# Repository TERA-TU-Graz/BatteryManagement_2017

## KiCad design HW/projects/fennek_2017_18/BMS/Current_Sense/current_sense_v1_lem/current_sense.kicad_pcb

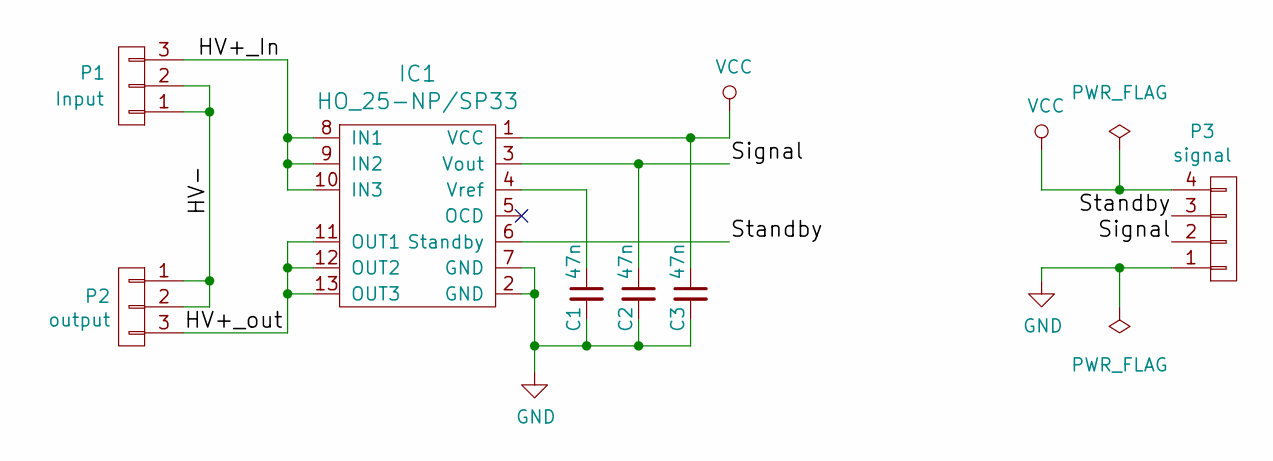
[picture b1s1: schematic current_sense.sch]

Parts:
C1, C2, C3: 47n; C_0603in
IC1: HO_25-NP/SP33; HO_25-NP_SP33
P1: Input; PhoenixContact_MSTBVA-G_03x5.08mm_Vertical
P2: output; PhoenixContact_MSTBA-G_03x5.08mm_Angled
P3: signal; Molex_PicoBlade_53261-0471_04x1.25mm_Angled

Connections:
/HV+_In: IC1.8 (IN1), IC1.9 (IN2), IC1.10 (IN3), P1.3
/HV+_out: IC1.11 (OUT1), IC1.12 (OUT2), IC1.13 (OUT3), P2.3
/HV-: P1.1, P1.2, P2.1, P2.2
/Signal: C2.1, IC1.3 (Vout), P3.2
/Standby: IC1.6 (Standby), P3.3
GND: C1.2, C2.2, C3.2, IC1.2 (GND), IC1.7 (GND), P3.1
unnamed: C1.1, IC1.4 (Vref)
VCC: C3.1, IC1.1 (VCC), P3.4

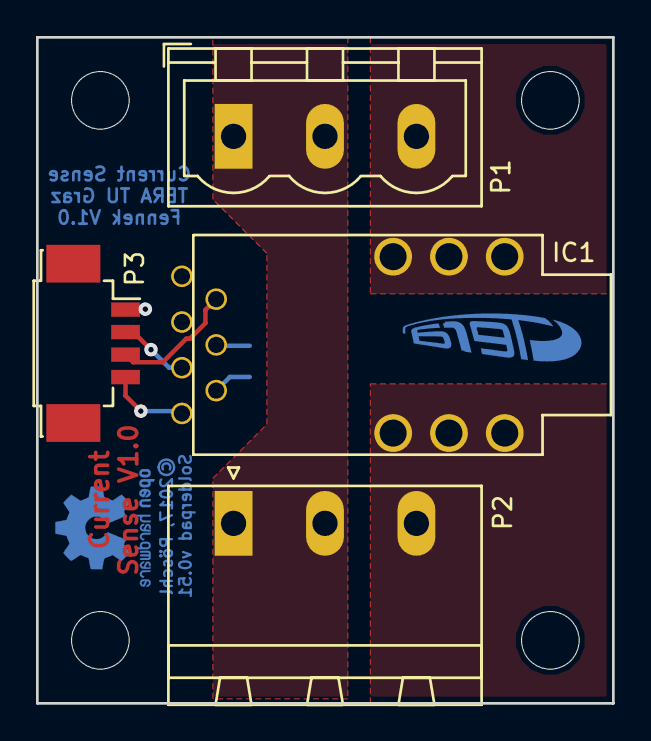
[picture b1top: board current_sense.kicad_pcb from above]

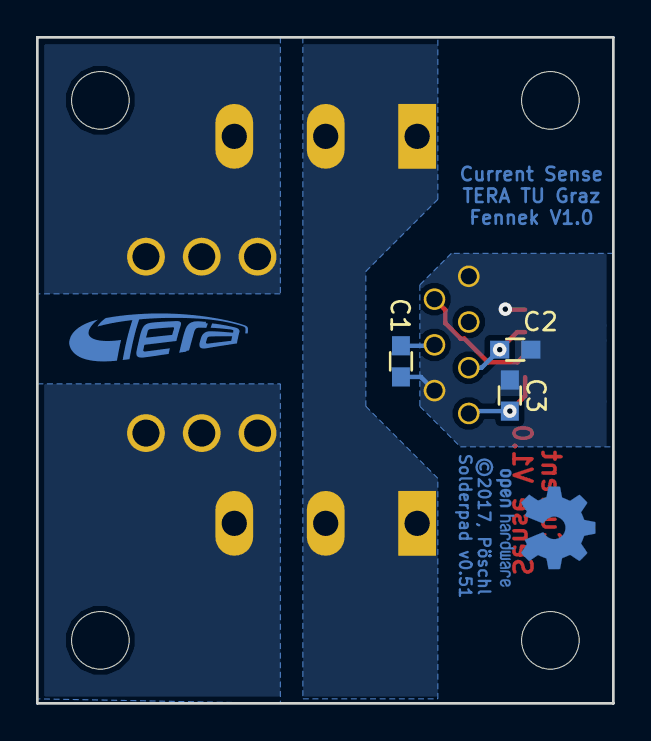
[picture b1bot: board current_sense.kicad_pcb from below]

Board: 2 copper layers, 32.0 x 37.0 mm, 8 parts (4 on the bottom side), 8 nets.

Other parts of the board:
svg2mod: G***; TERA_TextOnly_Cu_2.5x9.5mm

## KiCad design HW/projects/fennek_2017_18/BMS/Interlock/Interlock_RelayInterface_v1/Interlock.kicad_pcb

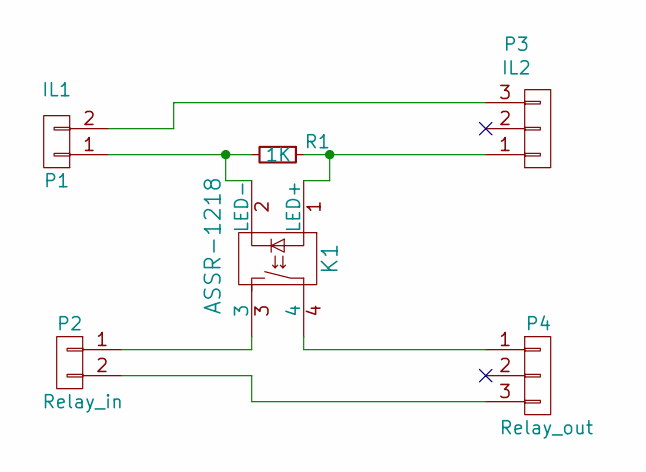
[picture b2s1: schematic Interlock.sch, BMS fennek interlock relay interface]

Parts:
K1: ASSR-1218; SO-4
P1: IL1; JST_EH_B02B-EH-A_02x2.50mm_Straight
P2: Relay_in; JST_XH_B02B-XH-A_02x2.50mm_Straight
P3: IL2; JST_EH_S03B-EH_03x2.50mm_Angled
P4: Relay_out; JST_XH_S03B-XH-A_03x2.50mm_Angled
R1: 1K; R_0603in

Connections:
unnamed: K1.1 (LED+), P3.1, R1.1
unnamed: K1.2 (LED-), P1.1, R1.2
unnamed: K1.3, P2.1
unnamed: K1.4, P4.1
unnamed: P1.2, P3.3
unnamed: P2.2, P4.3

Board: 2 copper layers, 6 parts (0 on the bottom side), 6 nets, no tracks yet.

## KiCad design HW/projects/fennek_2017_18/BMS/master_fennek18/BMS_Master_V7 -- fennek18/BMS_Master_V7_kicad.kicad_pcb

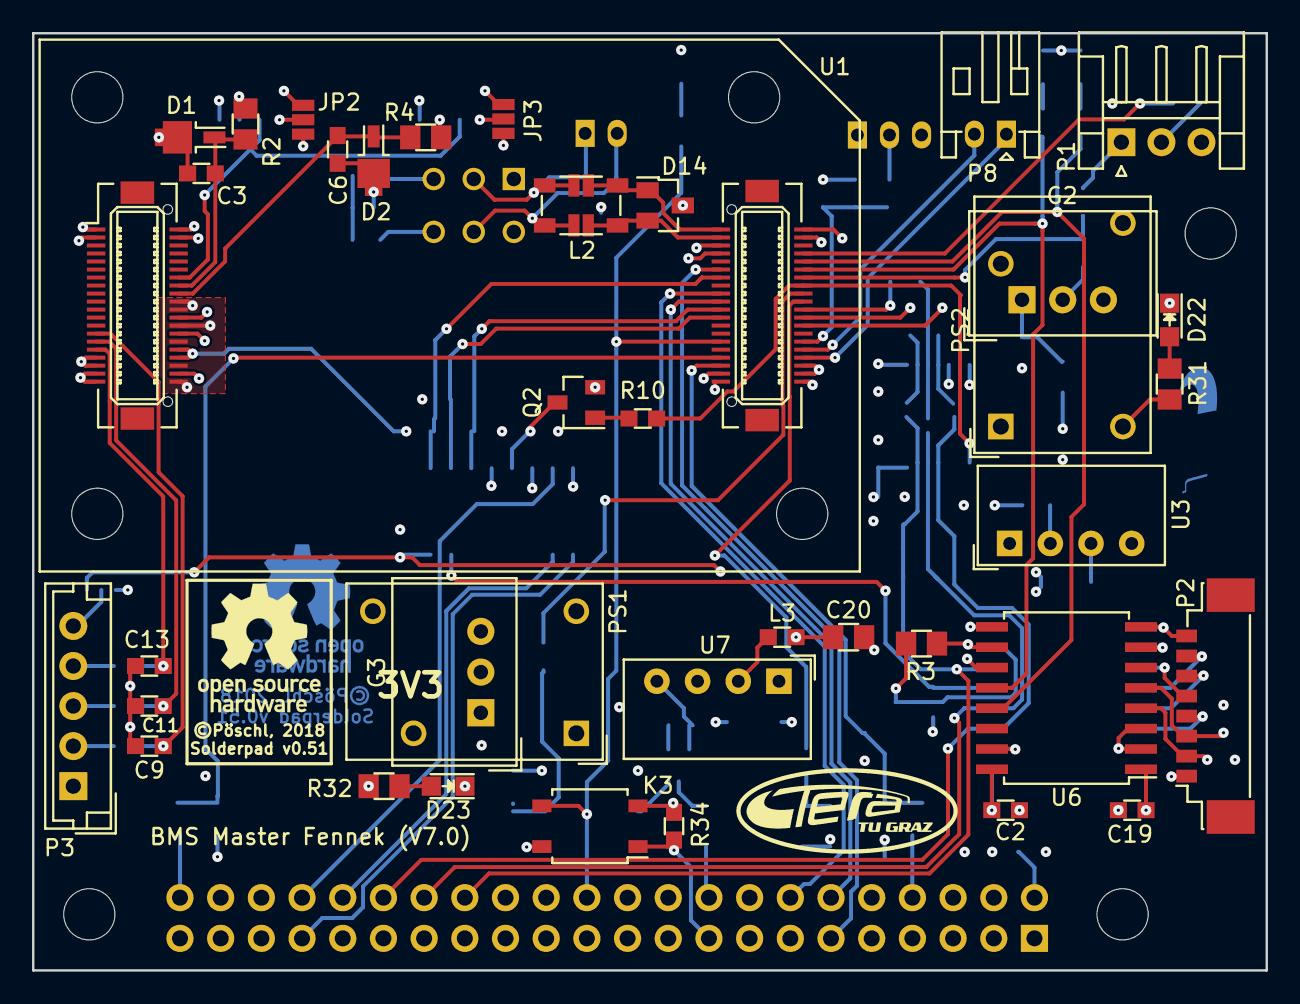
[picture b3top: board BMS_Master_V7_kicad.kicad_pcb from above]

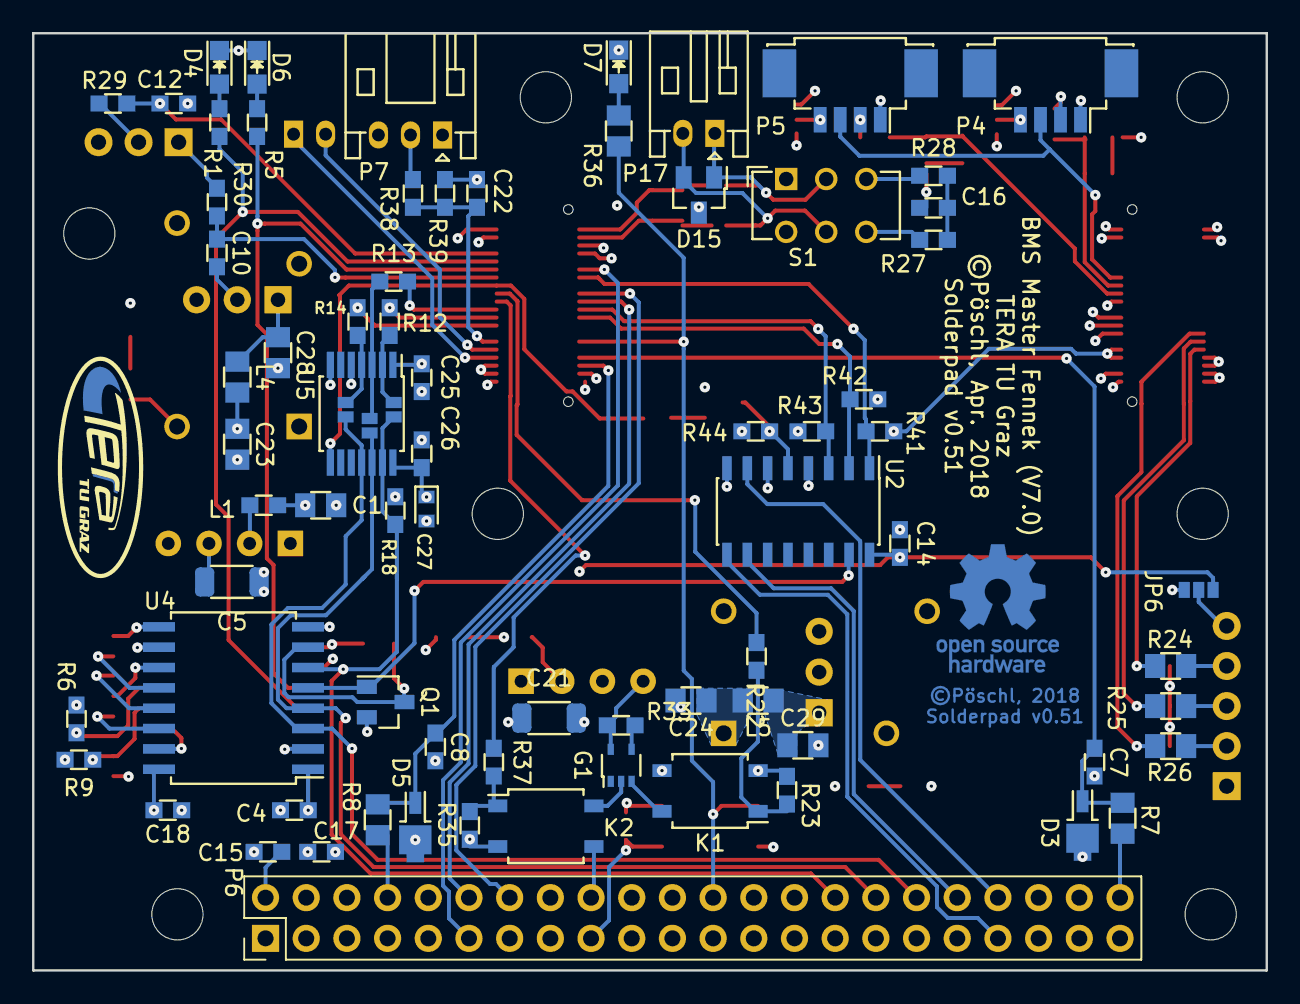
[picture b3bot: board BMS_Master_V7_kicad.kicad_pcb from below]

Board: 4 copper layers, 77.0 x 58.5 mm, 118 parts (77 on the bottom side), 92 nets.

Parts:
C1, C20: 4.7uF 25V; C_0805in
C2, C3, C4, C6, C7, C8, C9, C10, C11, C12, C13, C14, C15, C17, C18, C19, C22, C25, C26: 100n; C_0603in
C5, C21: 220pF 2kV; C_1206in_HV
C16: 47nF; C_0603in
C23, C24, C28, C29: 4u7; C_0805in
C27: 1u; TantalC_SizeM-1608mm_H0.9mm
D1, D2, D3, D5: 3V3; DO-216AA
D4: ~Alert; LED_0805
D6: ~Fault; LED_0805
D7: IL_OK; LED_0805
D14, D15: SUPPRESSOR; SOT-23
D22: 5V_OK; LED_0805
D23: 3V3_OK; LED_0805
G1: PSSI2021SAY
G2: TSR_0.5-2450; TSR_0.5
G3: TSR_0.5-2433; TSR_0.5
JP1, JP4, JP5: Jumper_NO_Small; SOLDERJUMPER_2_1mm
JP2, JP3: JUMPER3_NO; SOLDERJUMPER_3
JP6: JUMPER3_NO; SOLDERJUMPER_3_1mm
JP9, JP10: Jumper_NO_Small; SOLDERJUMPER_2
K1, K2, K3: ASSR-1218; SO-4
L1, L3: 4.7uH 50mA; L_0603in
L2: CM_CHOKE; L_ACT45B-XXX-2P_common-mode-choke
L4, L5: 3u3; L_0805in
P1: Buttons; JST_EH_S03B-EH_03x2.50mm_Angled
P2: Host_slave; Molex_PicoBlade_53398-0871_08x1.25mm_Straight
P3: ExtGPIO; JST_EH_B05B-EH-A_05x2.50mm_Straight
P4, P5: LEM; Molex_PicoBlade_53261-0471_04x1.25mm_Angled
P6: CONN_02X22; DW-22-08-L-D-200
P7: WheelSpeed; JST_PH_S3B-PH-K_03x2.00mm_Angled
P8, P17: CAN_CON_2pol; JST_PH_S2B-PH-K_02x2.00mm_Angled
PS1: Stepdown_v6-3V3; DCDC_Stepdown_v6
PS2: Stepdown_v6-5V; DCDC_Stepdown_v6
Q1, Q2: BSS205N
R1, R5: 5k1; R_0603in
R2, R4, R7, R8, R24, R25, R26: 1K; R_0805in
R3: 10k; R_0805in
R6, R9, R18: 100k; R_0603in
R10: 1k; R_0603in
R12, R13, R14: 100R; R_0603in
R22, R37: 470; R_0603in
R23, R29, R30, R34, R35: 1K; R_0603in
R27, R28: 60R; R_0603in
R31, R36: 5k1; R_0805in
R32: 2k2; R_0805in
R33: 120R; R_0603in
R38: 0R; R_0603in
R39: 22k; R_0603in
R41, R42, R43, R44: 10k; R_0603in
S1: SWITCH_DPDT; CuK_JS202011CQN_DPDT
U1: STM32f4_board_v3-1; STM32f4-board_v3-1
U2: SN74HC138DR
U3: Muarta_LME1205SC; Muarta_LME-SIP
U4, U6: ISO7241
U5: MAX3390EEUD
U7: Muarta_LME1212SC; Muarta_LME-SIP
svg2mod: G***; TERA_Logo_SilkS_5x12.5mm
svg2mod#2: G***; TERA_Logo_SilkS_and_Cu_5x12.5mm

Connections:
+3V3: C25.2, G3.3, JP2.3, JP3.3, JP6.1, P6.6, P6.42, PS1.2, R32.1, U1.2, U1.17, U1.18, U1.22, U1.27, U1.29, U1.39, U1.44, U1.59, U1.62, U1.63, U1.79, U5.1
+5V: C2.1, C4.1, C14.2, C26.1, C27.1, G2.3, JP2.1, JP3.1, JP6.3, K3.4, P1.3, P6.28, P7.3, PS2.2, R3.1, R31.1, R41.1, R42.1, R43.1, R44.2, U1.24, U1.25, U2.6, U2.16, U4.1, U5.14, U6.10, U6.16
+5V_SLAVE: C18.2, C19.2, P2.1, U3.4, U4.10, U4.16, U6.1, U6.7
+12V: C1.1, C17.2, C20.1, C23.1, C24.1, L1.2, L3.2, L4.2, L5.2, P6.4, PS1.1, PS2.1
/12V_Relay_Fault: P6.11, U1.46
/Alegro_1: P6.44, R7.1
/Alegro_1_Filtered: C7.1, D3.1, R7.2, U1.57
/Alegro_2: P6.8, R8.1
/Alegro_2_Filtered: C8.1, D5.1, R8.2, U1.58
/Button_Off: C10.1, R30.2, U1.74
/Button_On: C12.1, R29.2, U1.77
/CAN/CAN1+: P8.2, U1.65
/CAN/CAN1-: P8.1, U1.64
/CAN/CAN2+: D14.2, JP10.1, L2.2, U1.42
/CAN/CAN2-: D14.1, JP9.1, L2.3, U1.41
/CAN/CANperi+: D15.2, JP10.2, L2.1, P17.2, S1.5
/CAN/CANperi-: D15.1, JP9.2, L2.4, P17.1, S1.2
/CS_B0: R41.2, U1.47, U2.1
/CS_B1: R42.2, U1.52, U2.2
/CS_B2: R43.2, U1.51, U2.3
/EXT_GPIO_1: C13.1, R24.2, U1.16
/EXT_GPIO_2: C11.1, R25.2, U1.15
/EXT_GPIO_3: C9.1, R26.2, U1.14
/IL_next+: K2.3, P6.18
/IL_next-: K3.1, P6.17, R34.1
/Interlock/IL_Iconst: G1.2, K2.4
/Interlock_OK: K3.3, P6.24, R36.2, U1.55
/Interlock_On1: R22.2, U1.72
/Interlock_On2: R37.1, U1.71
/LEM1: C3.1, D1.1, R2.2, U1.33
/LEM2: C6.1, D2.1, R4.2, U1.32
/LEM_Standby: P4.3, P5.3, U1.34
/MISO: R12.2, U1.69
/MOSI: R13.2, U1.70
/Main Connector/+12VDC_BMS_Switched: C15.2, P6.2
/Main_Fault: P6.12, U1.50
/NALERT: R1.1, U1.76, U6.13
/NCS_12V_Relay: P6.37, U2.9
/NCS_MainRelay: P6.36, U2.10
/NCS_PreCharge: P6.38, U2.7
/NFAULT: R5.1, U1.75, U6.12
/Precharge_Fault: P6.14, U1.49
/SCLK: R14.2, U1.68
/SPI_CLK_5V: JP5.2, P6.34, U4.3, U5.11
/SPI_CS: R10.2, U1.73, U5.8
/SPI_Controller/MISO_1: JP1.1, R12.1, U5.2
/SPI_Controller/MOSI_1: JP4.1, R13.1, U5.3
/SPI_Controller/NCS1: Q1.1, U2.15, U4.5
/SPI_Controller/SCLK_1: JP5.1, R14.1, U5.4
/SPI_Controller/SPI Isolator/MISO_slave: P2.5, U4.11
/SPI_Controller/SPI Isolator/MOSI_Slave: P2.6, U4.13
/SPI_Controller/SPI Isolator/NCS_Slave: P2.7, U4.12
/SPI_Controller/SPI Isolator/SCLK_slave: P2.4, U4.14
/SPI_Controller/SPI Isolator/~Alert_slave: P2.2, R9.1, U6.4
/SPI_Controller/SPI Isolator/~Fault_slave: P2.3, R6.1, U6.5
/SPI_Controller/SPI_NCS_5V: Q2.3, R44.1, U2.5
/SPI_MISO_5V: JP1.2, P6.30, R18.1, U4.6, U5.13
/SPI_MOSI_5V: JP4.2, P6.32, U4.4, U5.12
/WheelSpeed: C22.1, R38.2, R39.2, U1.66
GND: C1.2, C2.2, C3.2, C4.2, C5.1, C6.2, C7.2, C8.2, C9.2, C10.2, C11.2, C12.2, C13.2, C14.1, C15.1, C16.2, C17.1, C20.2, C21.1, C22.2, C23.2, C24.2, C25.1, C26.2, C27.2, C28.2, C29.2, D1.2, D2.2, D3.2, D4.1, D5.2, D6.1, D7.1, D14.3, D15.3, D22.1, D23.1, G2.2, G3.2, K1.2, K2.2, P3.1, P4.1, P5.1, P6.1, P6.3, P6.5, P6.7, P6.9, P6.10, P6.13, P6.21, P6.22, P6.23, P6.25, P6.26, P6.27, P6.29, P6.31, P6.33, P6.35, P6.39, P6.40, P6.41, P6.43, P7.1, PS1.3, PS1.4, PS2.3, PS2.4, Q1.2, Q2.2, R18.2, R23.2, R35.2, R39.1, U1.1, U1.19, U1.20, U1.21, U1.23, U1.26, U1.28, U1.30, U1.31, U1.40, U1.43, U1.60, U1.61, U1.80, U2.4, U2.8, U3.1, U4.2, U4.8, U5.5, U5.7, U6.9, U6.11, U6.15, U7.1
GND_slave: C5.2, C18.1, C19.1, P2.8, R6.2, R9.2, U3.3, U4.9, U4.15, U6.2, U6.3, U6.8
IL_V+: G1.5, R33.1, U7.4
IL_V-: C21.2, K1.3, K3.2, R34.2, U7.3
unnamed: C16.1, R27.2, R28.2
unnamed: C28.1, G2.1, L4.1
unnamed: C29.1, G3.1, L5.1
unnamed: D4.2, R1.2
unnamed: D6.2, R5.2
unnamed: D7.2, R36.1
unnamed: D22.2, R31.2
unnamed: D23.2, R32.2
unnamed: G1.3, K1.4
unnamed: G1.4, R33.2
unnamed: JP2.2, P4.4
unnamed: JP3.2, P5.4
unnamed: JP6.2, P3.5
unnamed: K1.1, R22.1, R23.1
unnamed: K2.1, R35.1, R37.2
unnamed: L1.1, U3.2
unnamed: L3.1, U7.2
unnamed: P1.1, R30.1
unnamed: P1.2, R29.1
unnamed: P3.2, R26.1
unnamed: P3.3, R25.1
unnamed: P3.4, R24.1
unnamed: P4.2, R2.1
unnamed: P5.2, R4.1
unnamed: P7.2, R38.1
unnamed: Q1.3, R3.2, U4.7
unnamed: Q2.1, R10.1
unnamed: R27.1, S1.6
unnamed: R28.1, S1.3

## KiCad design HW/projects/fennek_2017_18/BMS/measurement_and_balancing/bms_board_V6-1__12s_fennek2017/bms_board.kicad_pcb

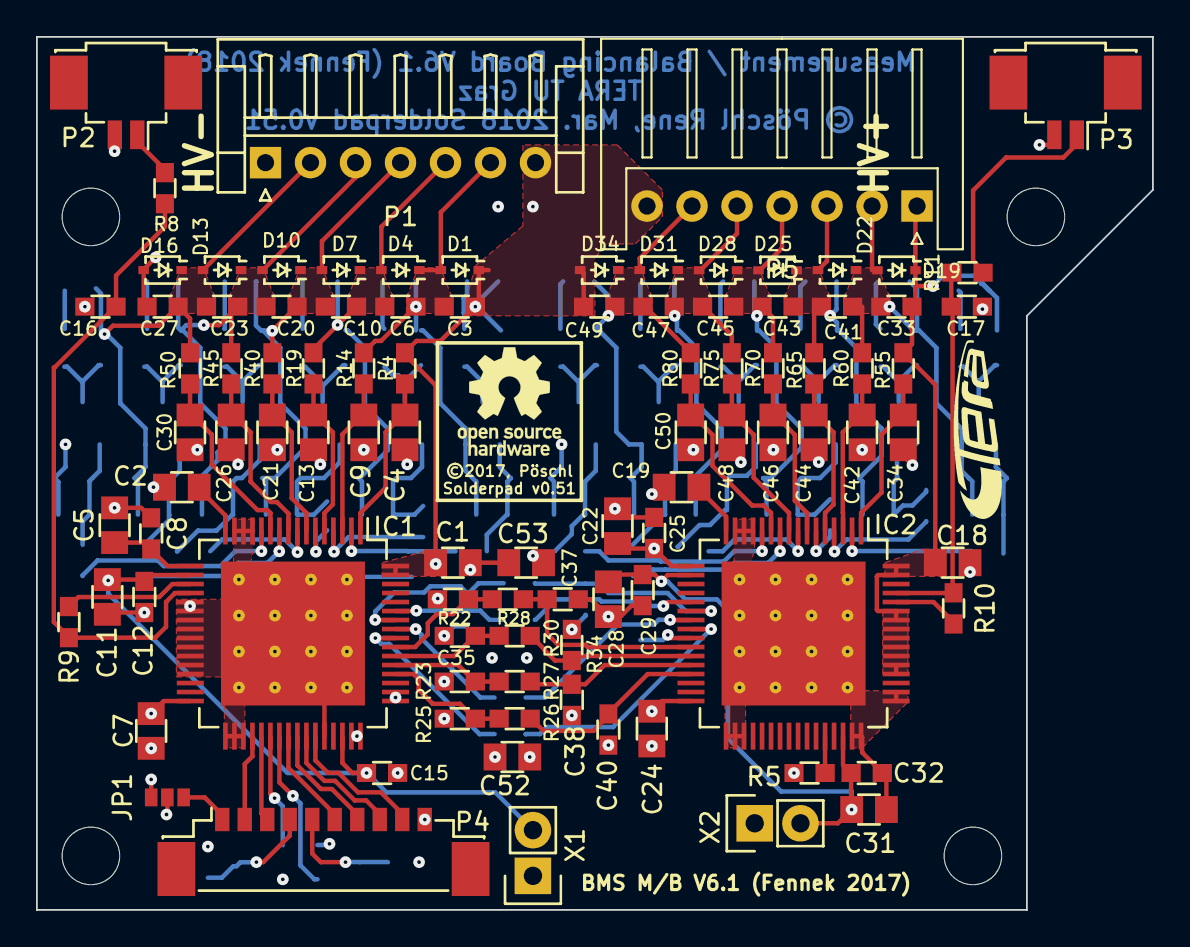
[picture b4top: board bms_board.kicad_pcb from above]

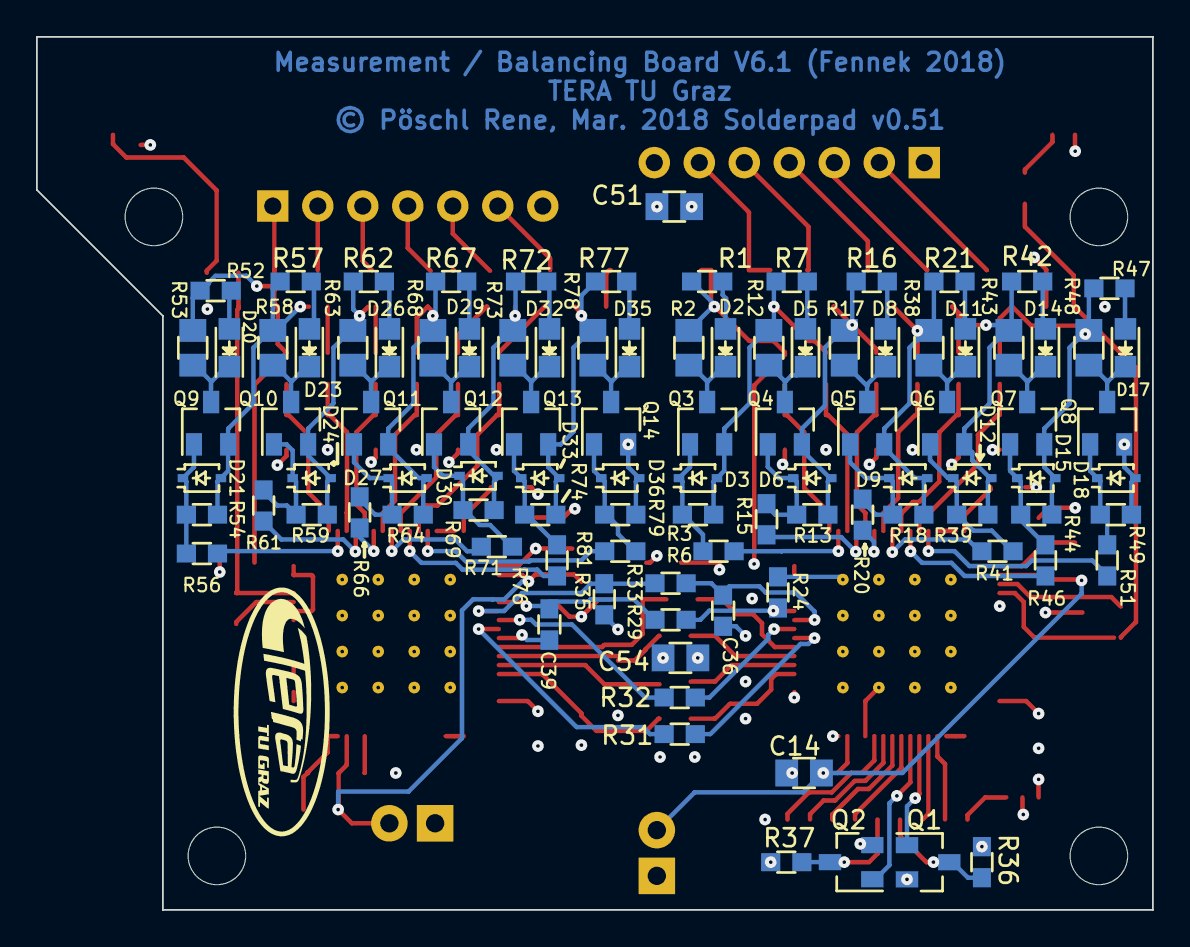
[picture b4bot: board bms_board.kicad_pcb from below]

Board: 4 copper layers, 62.0 x 48.5 mm, 197 parts (100 on the bottom side), 116 nets.

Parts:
C1, C4, C9, C13, C18, C21, C26, C30, C34, C42, C44, C46, C48, C50, C51, C52, C53, C54: 100n 50V; C_0805in
C2, C19: 10u; C_0805in
C3, C6, C8, C10, C12, C15, C20, C23, C25, C27, C29, C32, C33, C41, C43, C45, C47, C49: 100n; C_0603in
C5, C7, C11, C14, C22, C24, C28, C31: 2.2u; C_0805in
C16, C17: 47n; C_0603in
C35, C36, C37, C38, C39, C40: 33p; C_0603in
D1, D3, D4, D6, D7, D9, D10, D12, D13, D15, D16, D18, D19, D21, D22, D24, D25, D27, D28, D30, D31, D33, D34, D36: 5.1V; SOD-323
D2, D5, D8, D11, D14, D17, D20, D23, D26, D29, D32, D35: LED; LED_0805
IC1, IC2: TI-bq76pl536; TI_bq76PL536
JP1: JUMPER3_NO; SOLDERJUMPER_3_1mm
P1: CONN_01X07; JST_EH_S07B-EH_07x2.50mm_Angled
P2: TS1; Molex_PicoBlade_53261-0271_02x1.25mm_Angled
P3: TS2; Molex_PicoBlade_53261-0271_02x1.25mm_Angled
P4: Host_Interface; Molex_PicoBlade_53398-1071_10x1.25mm_Straight
P5: CONN_01X07; JST_XH_S07B-XH-A_07x2.50mm_Angled
Q1, Q2, Q3, Q4, Q5, Q6, Q7, Q8, Q9, Q10, Q11, Q12, Q13, Q14: BSS205N
R1, R7, R16, R21, R42, R47, R52, R57, R62, R67, R72, R77: 2K2; R_0603in
R2, R12, R17, R38, R43, R48, R53, R58, R63, R68, R73, R78: 180R; R_0805in
R3, R13, R18, R22, R23, R24, R25, R39, R44, R49, R54, R59, R64, R69, R74, R79: 2M; R_0603in
R4, R6, R14, R15, R19, R20, R26, R27, R28, R29, R30, R31, R32, R33, R40, R41, R45, R46, R50, R51, R55, R56, R60, R61, R65, R66, R70, R71, R75, R76, R80, R81: 1K; R_0603in
R5: 100K; R_0603in
R8, R11: 1.47K; R_0603in
R9, R10: 1.82K; R_0603in
R34, R35: 510K; R_0603in
R36, R37: 10K; R_0603in
X1, X2: Prog_Voltage; Socket_Strip_Straight_1x02
svg2mod: G***; TERA_Logo_SilkS_5x12.5mm
svg2mod#2: G***; TERA_TextOnly_SilkS_2.5x9.5mm

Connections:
+5V: C7.1, C16.1, IC1.32, JP1.1, P2.2
+BATT: C18.2, C33.1, D19.1, IC2.52, IC2.53, IC2.54, IC2.55, IC2.56, IC2.57, IC2.58, IC2.59, IC2.63, IC2.64, P5.1, R52.1, R53.1, R55.2
/5V_C2: C17.1, C24.1, IC2.32, P3.2, R34.1, R35.1
/Chip1/+5V_LDOA: C5.1, C8.1, IC1.17
/Chip1/Alert_H: IC1.38, Q1.1
/Chip1/BalanceCell1/VCn: C30.1, IC1.11, R50.1
/Chip1/BalanceCell2/VCn: C26.1, IC1.9, R45.1
/Chip1/BalanceCell3/VCn: C21.1, IC1.7, R40.1
/Chip1/BalanceCell4/VCn: C13.1, IC1.5, R19.1
/Chip1/BalanceCell5/VCn: C9.1, IC1.3, R14.1
/Chip1/BalanceCell6/VCn: C4.1, IC1.1, R4.1
/Chip1/CB1: IC1.12, R51.1
/Chip1/CB2: IC1.10, R46.1
/Chip1/CB3: IC1.8, R41.1
/Chip1/CB4: IC1.6, R20.1
/Chip1/CB5: IC1.4, R15.1
/Chip1/CB6: IC1.2, R6.1
/Chip1/CONV_H: IC1.36, P4.2
/Chip1/CS_H: IC1.43, P4.9
/Chip1/DRDY_H: IC1.37, P4.3
/Chip1/Fault_H: IC1.39, Q2.1
/Chip1/LDODx: C11.1, C12.1, C14.1, C15.1, IC1.18, IC1.46, X1.2
/Chip1/SCLK_H: IC1.40, P4.6
/Chip1/SDI_H: IC1.42, P4.8
/Chip1/SDO_H: IC1.41, P4.7
/Chip1/TS1+: C16.2, IC1.20, R8.1, R9.1
/Chip1/TS1-: IC1.19, R9.2
/Chip1/VC1: C23.2, C27.1, D13.2, D15.2, D16.1, P1.2, Q7.2, R44.2, R47.1, R48.1, R50.2
/Chip1/VC2: C20.2, C23.1, D10.2, D12.2, D13.1, P1.3, Q6.2, R39.2, R42.1, R43.1, R45.2
/Chip1/VC3: C10.2, C20.1, D7.2, D9.2, D10.1, P1.4, Q5.2, R18.2, R21.1, R38.1, R40.2
/Chip1/VC4: C6.2, C10.1, D4.2, D6.2, D7.1, P1.5, Q4.2, R13.2, R16.1, R17.1, R19.2
/Chip1/VC5: C3.2, C6.1, D1.2, D3.2, D4.1, P1.6, Q3.2, R3.2, R7.1, R12.1, R14.2
/Chip2/+5V_LDOA: C22.1, C25.1, IC2.17, R5.1
/Chip2/BalanceCell1/VCn: C50.1, IC2.11, R80.1
/Chip2/BalanceCell2/VCn: C48.1, IC2.9, R75.1
/Chip2/BalanceCell3/VCn: C46.1, IC2.7, R70.1
/Chip2/BalanceCell4/VCn: C44.1, IC2.5, R65.1
/Chip2/BalanceCell5/VCn: C42.1, IC2.3, R60.1
/Chip2/BalanceCell6/VCn: C34.1, IC2.1, R55.1
/Chip2/CB1: IC2.12, R81.1
/Chip2/CB2: IC2.10, R76.1
/Chip2/CB3: IC2.8, R71.1
/Chip2/CB4: IC2.6, R66.1
/Chip2/CB5: IC2.4, R61.1
/Chip2/CB6: IC2.2, R56.1
/Chip2/HSEL: IC2.44, R5.2
/Chip2/LDODx: C28.1, C29.1, C31.1, C32.1, IC2.18, IC2.46, X2.2
/Chip2/TS2+: C17.2, IC2.61, R10.1, R11.1
/Chip2/TS2-: IC2.60, R10.2
/Chip2/VC1: C47.2, C49.1, D31.2, D33.2, D34.1, P5.6, Q13.2, R74.2, R77.1, R78.1, R80.2
/Chip2/VC2: C45.2, C47.1, D28.2, D30.2, D31.1, P5.5, Q12.2, R69.2, R72.1, R73.1, R75.2
/Chip2/VC3: C43.2, C45.1, D25.2, D27.2, D28.1, P5.4, Q11.2, R64.2, R67.1, R68.1, R70.2
/Chip2/VC4: C41.2, C43.1, D22.2, D24.2, D25.1, P5.3, Q10.2, R59.2, R62.1, R63.1, R65.2
/Chip2/VC5: C33.2, C41.1, D19.2, D21.2, D22.1, P5.2, Q9.2, R54.2, R57.1, R58.1, R60.2
/Daisychain/Alert_1: IC1.57, R32.1
/Daisychain/Alert_2: IC2.23, R32.2
/Daisychain/CONV_1: IC1.59, R24.2, R29.1
/Daisychain/CONV_2: C39.1, IC2.21, R29.2
/Daisychain/CS_1: IC1.52, R25.2, R26.1
/Daisychain/CS_2: C40.1, IC2.29, R26.2
/Daisychain/DRDY_1: C36.2, IC1.58, R33.1
/Daisychain/DRDY_2: IC2.22, R33.2, R35.2
/Daisychain/Fault_1: IC1.56, R31.1
/Daisychain/Fault_2: IC2.24, R31.2
/Daisychain/SCLK_1: IC1.55, R22.2, R28.1
/Daisychain/SCLK_2: C37.1, IC2.26, R28.2
/Daisychain/SDI_1: IC1.53, R23.2, R27.1
/Daisychain/SDI_2: C38.1, IC2.28, R27.2
/Daisychain/SDO_1: C35.2, IC1.54, R30.1
/Daisychain/SDO_2: IC2.27, R30.2, R34.2
/Host_connect/+5V_DO: JP1.2, R36.1, R37.1
/Host_connect/+5V_Host: JP1.3, P4.1
/Host_connect/NALERT_H: P4.4, Q1.3, R36.2
/Host_connect/NFAULT_H: P4.5, Q2.3, R37.2
GND: C1.1, C2.2, C4.2, C5.2, C7.2, C8.2, C9.2, C11.2, C12.2, C13.2, C14.2, C15.2, C21.2, C26.2, C27.2, C30.2, C51.2, C52.2, C53.2, C54.2, D16.2, D18.2, IC1.13, IC1.14, IC1.15, IC1.21, IC1.22, IC1.23, IC1.24, IC1.25, IC1.26, IC1.27, IC1.28, IC1.29, IC1.33, IC1.34, IC1.35, IC1.44, IC1.47, IC1.48, IC1.49, IC1.50, IC1.65, P1.1, P4.10, Q1.2, Q2.2, Q8.2, R22.1, R23.1, R24.1, R25.1, R49.2, X1.1
unnamed: C2.1, IC1.16
unnamed: C19.1, IC2.16
unnamed: D2.1, Q3.3, R2.2
unnamed: D2.2, R1.2
unnamed: D3.1, Q3.1, R3.1, R6.2
unnamed: D5.1, Q4.3, R12.2
unnamed: D5.2, R7.2
unnamed: D6.1, Q4.1, R13.1, R15.2
unnamed: D8.1, Q5.3, R17.2
unnamed: D8.2, R16.2
unnamed: D9.1, Q5.1, R18.1, R20.2
unnamed: D11.1, Q6.3, R38.2
unnamed: D11.2, R21.2
unnamed: D12.1, Q6.1, R39.1, R41.2
unnamed: D14.1, Q7.3, R43.2
unnamed: D14.2, R42.2
unnamed: D15.1, Q7.1, R44.1, R46.2
unnamed: D17.1, Q8.3, R48.2
unnamed: D17.2, R47.2
unnamed: D18.1, Q8.1, R49.1, R51.2
unnamed: D20.1, Q9.3, R53.2
unnamed: D20.2, R52.2
unnamed: D21.1, Q9.1, R54.1, R56.2
unnamed: D23.1, Q10.3, R58.2
unnamed: D23.2, R57.2
unnamed: D24.1, Q10.1, R59.1, R61.2
unnamed: D26.1, Q11.3, R63.2
unnamed: D26.2, R62.2
unnamed: D27.1, Q11.1, R64.1, R66.2
unnamed: D29.1, Q12.3, R68.2
unnamed: D29.2, R67.2
unnamed: D30.1, Q12.1, R69.1, R71.2
unnamed: D32.1, Q13.3, R73.2
unnamed: D32.2, R72.2
unnamed: D33.1, Q13.1, R74.1, R76.2
unnamed: D35.1, Q14.3, R78.2
unnamed: D35.2, R77.2
unnamed: D36.1, Q14.1, R79.1, R81.2
unnamed: P2.1, R8.2
unnamed: P3.1, R11.2
Vmiddle: C1.2, C3.1, C18.1, C19.2, C22.2, C24.2, C25.2, C28.2, C29.2, C31.2, C32.2, C34.2, C35.1, C36.1, C37.2, C38.2, C39.2, C40.2, C42.2, C44.2, C46.2, C48.2, C49.2, C50.2, C51.1, C52.1, C53.1, C54.1, D1.1, D34.2, D36.2, IC1.63, IC1.64, IC2.13, IC2.14, IC2.15, IC2.25, IC2.33, IC2.34, IC2.35, IC2.47, IC2.48, IC2.49, IC2.50, IC2.65, P1.7, P5.7, Q14.2, R1.1, R2.1, R4.2, R79.2, X2.1

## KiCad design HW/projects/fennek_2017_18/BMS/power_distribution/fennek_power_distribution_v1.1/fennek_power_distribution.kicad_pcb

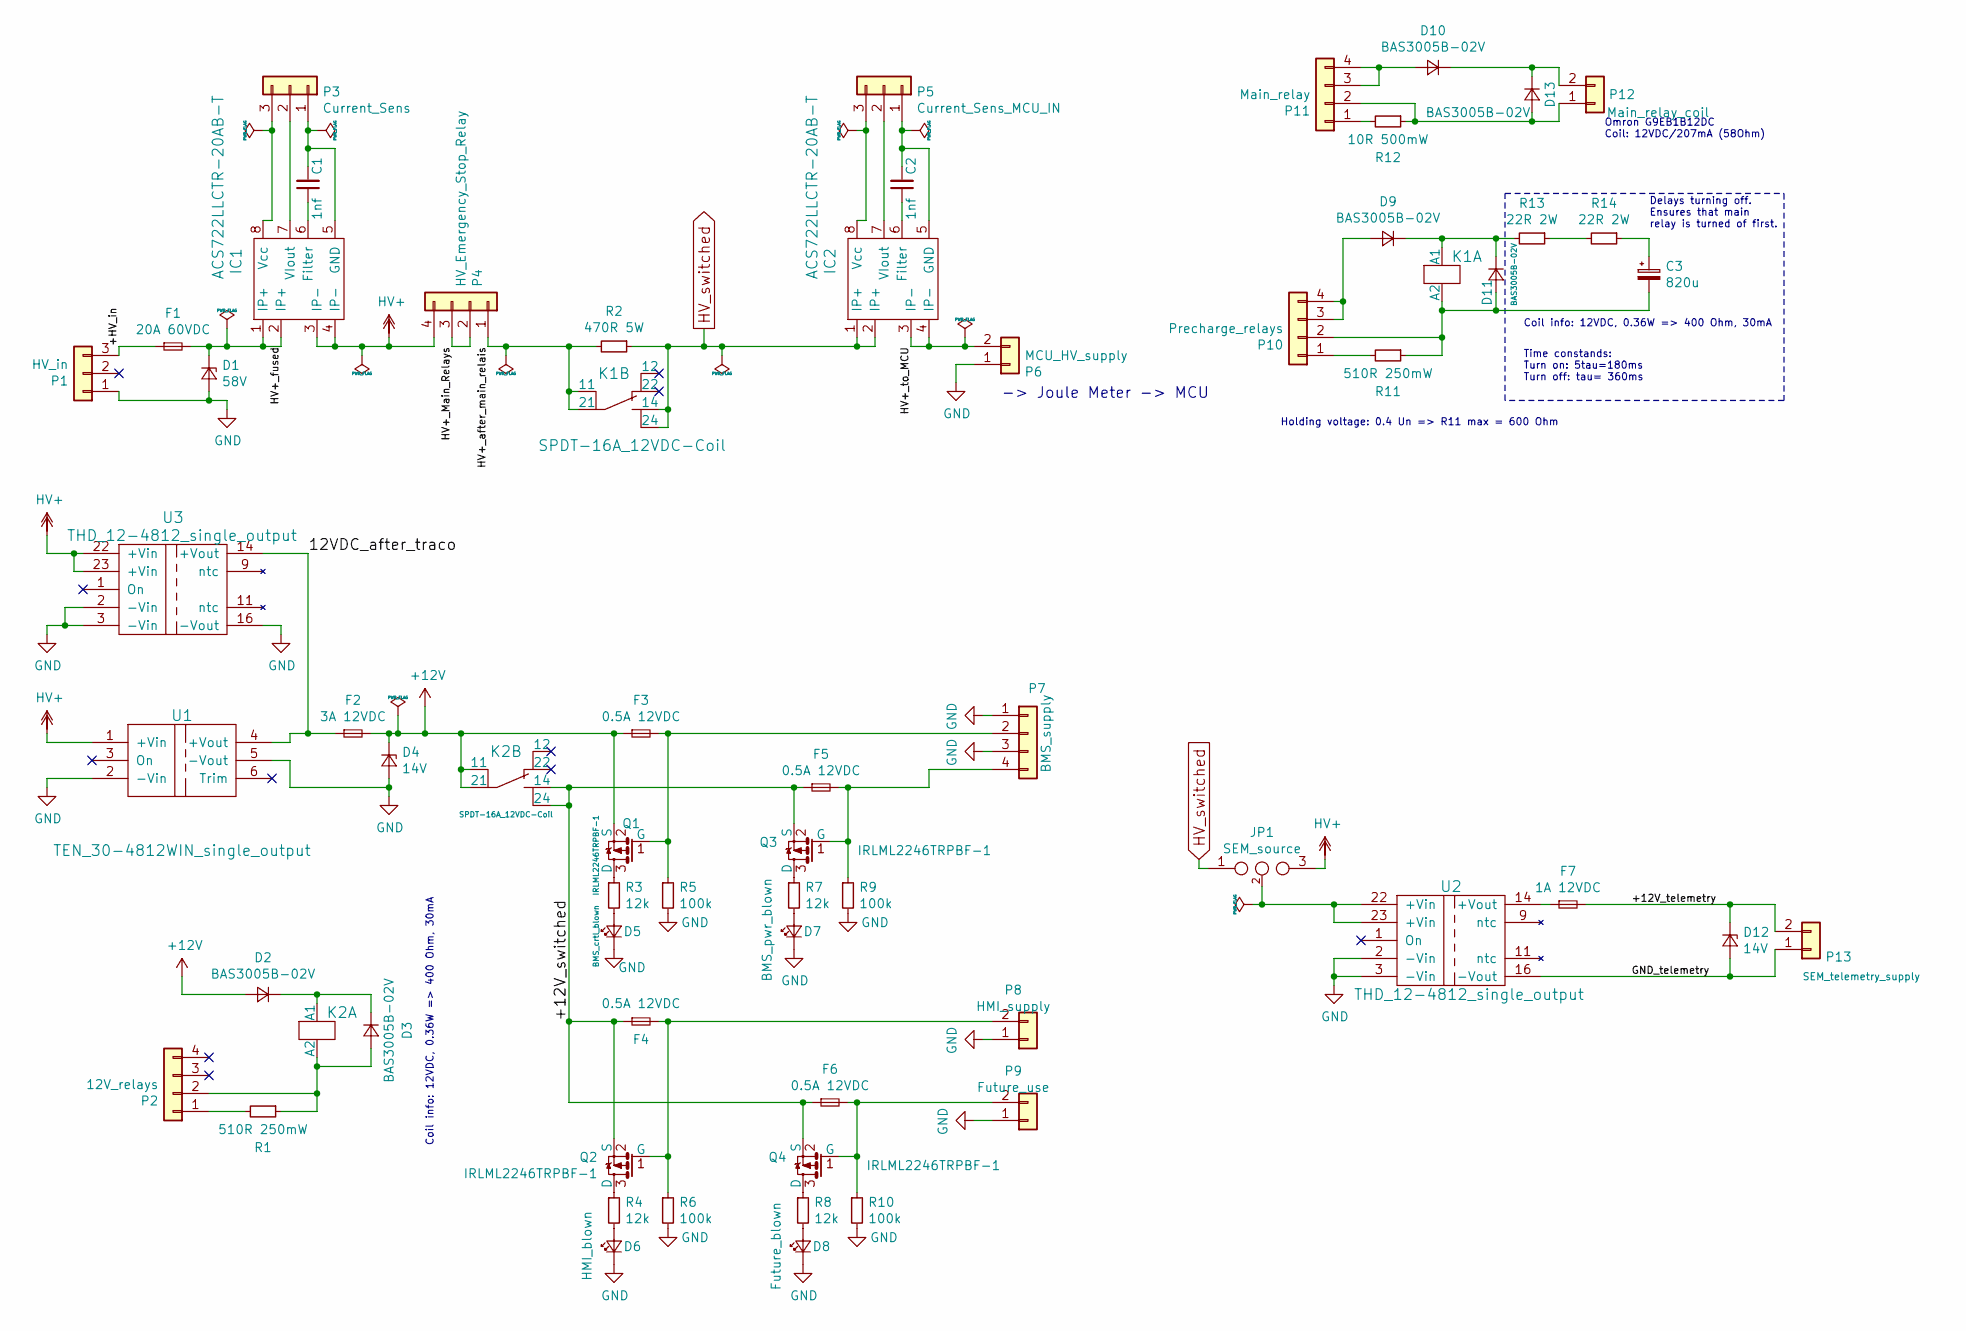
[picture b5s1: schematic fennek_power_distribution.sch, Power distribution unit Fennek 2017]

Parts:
C1, C2: 1nf; C_0603in
C3: 820u; c_elec_10x10mm
D1: 58V; DO-214AA_with_vias_in_pad
D2, D3, D9, D10, D11, D13: BAS3005B-02V; BAS3005B-02V__sc79
D4, D12: 14V; SOD128_with_vias_in_pad
D5: BMS_crtl_blown; LED_0805
D6: HMI_blown; LED_0805
D7: BMS_pwr_blown; LED_0805
D8: Future_blown; LED_0805
F1: 20A 60VDC; Fuse_holder_6.3x32mm_Schruter_0031.2520
F2: 3A 12VDC; Fuse_Phoenix_SI-H-FKS_15
F3, F4, F5, F6: 0.5A 12VDC; Fuse_0603in
F7: 1A 12VDC; Fuse_Phoenix_SI-H-FKS_15
IC1, IC2: ACS722LLCTR-20AB-T; ACS7xx
JP1: SEM_source; SOLDERJUMPER_3
K1, K2: SPDT-16A_12VDC-Coil; Finder-41.61.9.012.0010_SPDT-16A_12VDC-Coil
P1: HV_in; PhoenixContact_MSTBA-G_03x5.08mm_Angled
P2: 12V_relays; JST_EH_B04B-EH-A_04x2.50mm_Straight
P3: Current_Sens; Molex_PicoBlade_53398-0371_03x1.25mm_Straight
P4: HV_Emergency_Stop_Relay; PhoenixContact_MSTBA-G_04x5.08mm_Angled
P5: Current_Sens_MCU_IN; Molex_PicoBlade_53398-0371_03x1.25mm_Straight
P6: MCU_HV_supply; PhoenixContact_MSTB-GF_02x5.08mm_Angled_ThreadedFlange
P7: BMS_supply; JST_XH_B04B-XH-A_04x2.50mm_Straight
P8: HMI_supply; JST_XH_B02B-XH-A_02x2.50mm_Straight
P9: Future_use; JST_XH_B02B-XH-A_02x2.50mm_Straight
P10: Precharge_relays; JST_EH_B04B-EH-A_04x2.50mm_Straight
P11: Main_relay; JST_EH_B04B-EH-A_04x2.50mm_Straight
P12: Main_relay_coil; JST_EH_B02B-EH-A_02x2.50mm_Straight
P13: SEM_telemetry_supply; PhoenixContact_MC-GF_02x3.50mm_Angled_ThreadedFlange
Q1, Q2, Q3, Q4: IRLML2246TRPBF-1
R1, R11: 510R 250mW; R_1206in
R2: 470R 5W; TE_SMW-5W
R3, R4, R7, R8: 12k; R_0603in
R5, R6, R9, R10: 100k; R_0603in
R12: 10R 500mW; R_1210in
R13, R14: 22R 2W; R_2512in
U1: TEN_30-4812WIN_single_output; TEN_30-xxxx
U2, U3: THD_12-4812_single_output; THD_12-xxxx

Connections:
+12V: D2.2 (A), D4.1 (K), F2.2, F3.1, K2.5 (11), K2.6 (21), Q1.2 (S)
/12VDC_after_traco: F2.1, U1.4 (+Vout), U3.14 (+Vout)
/+12V_switched: F4.1, F5.1, F6.1, K2.7 (14), K2.8 (24), Q2.2 (S), Q3.2 (S), Q4.2 (S)
/+12V_telemetry: D12.1 (K), F7.2, P13.2
/+HV_in: F1.1, P1.3
/GND_telemetry: D12.2 (A), P13.1, U2.16 (-Vout)
/HV+_Main_Relays: P4.2, P4.3
/HV+_after_main_relais: K1.5 (11), K1.6 (21), P4.1, R2.2
/HV+_fused: D1.1 (K), F1.2, IC1.1 (IP+), IC1.2 (IP+)
/HV+_to_MCU: IC2.3 (IP-), IC2.4 (IP-), P6.2
GND: D1.2 (A), D4.2 (A), D5.1 (K), D6.1 (K), D7.1 (K), D8.1 (K), P1.1, P6.1, P7.1, P7.3, P8.1, P9.1, R5.2, R6.2, R9.2, R10.2, U1.2 (-Vin), U1.5 (-Vout), U2.2 (-Vin), U2.3 (-Vin), U3.2 (-Vin), U3.3 (-Vin), U3.16 (-Vout)
HV+: IC1.3 (IP-), IC1.4 (IP-), JP1.3, P4.4, U1.1 (+Vin), U3.22 (+Vin), U3.23 (+Vin)
HV_switched: IC2.1 (IP+), IC2.2 (IP+), JP1.1 (m), K1.7 (14), K1.8 (24), R2.1
unnamed: C1.1, IC1.6 (Filter)
unnamed: C1.2, IC1.5 (GND), P3.1
unnamed: C2.1, IC2.6 (Filter)
unnamed: C2.2, IC2.5 (GND), P5.1
unnamed: C3.1, R14.1
unnamed: C3.2, D11.2 (A), K1.2 (A2), P10.2, R11.1
unnamed: D2.1 (K), D3.1 (K), K2.1 (A1)
unnamed: D3.2 (A), K2.2 (A2), P2.2, R1.1
unnamed: D5.2 (A), R3.2
unnamed: D6.2 (A), R4.2
unnamed: D7.2 (A), R7.2
unnamed: D8.2 (A), R8.2
unnamed: D9.2 (A), P10.3, P10.4
unnamed: D10.1 (K), D13.1 (K), P12.2
unnamed: D10.2 (A), P11.3, P11.4
unnamed: D9.1 (K), D11.1 (K), K1.1 (A1), R13.2
unnamed: D13.2 (A), P11.2, P12.1, R12.1
unnamed: F3.2, P7.2, Q1.1 (G), R5.1
unnamed: F4.2, P8.2, Q2.1 (G), R6.1
unnamed: F5.2, P7.4, Q3.1 (G), R9.1
unnamed: F6.2, P9.2, Q4.1 (G), R10.1
unnamed: F7.1, U2.14 (+Vout)
unnamed: IC1.7 (VIout), P3.2
unnamed: IC1.8 (Vcc), P3.3
unnamed: IC2.7 (VIout), P5.2
unnamed: IC2.8 (Vcc), P5.3
unnamed: JP1.2, U2.22 (+Vin), U2.23 (+Vin)
unnamed: P2.1, R1.2
unnamed: P10.1, R11.2
unnamed: P11.1, R12.2
unnamed: Q1.3 (D), R3.1
unnamed: Q2.3 (D), R4.1
unnamed: Q3.3 (D), R7.1
unnamed: Q4.3 (D), R8.1
unnamed: R13.1, R14.2

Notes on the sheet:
Delays turning off. Ensures that main relay is turned of first.
Omron G9EB1B12DC Coil: 12VDC/207mA (58Ohm)
Coil info: 12VDC, 0.36W => 400 Ohm, 30mA
Time constands: Turn on: 5tau=180ms Turn off: tau= 360ms
-> Joule Meter -> MCU
Holding voltage: 0.4 Un => R11 max = 600 Ohm

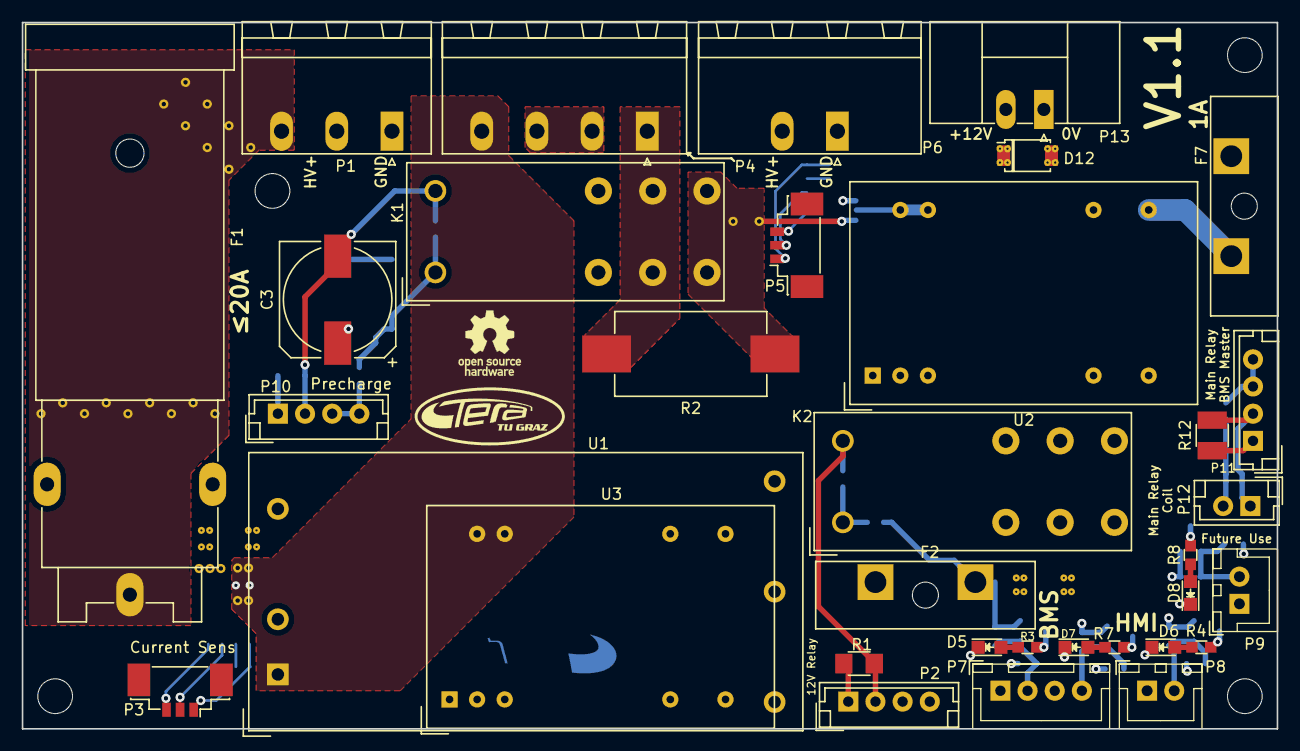
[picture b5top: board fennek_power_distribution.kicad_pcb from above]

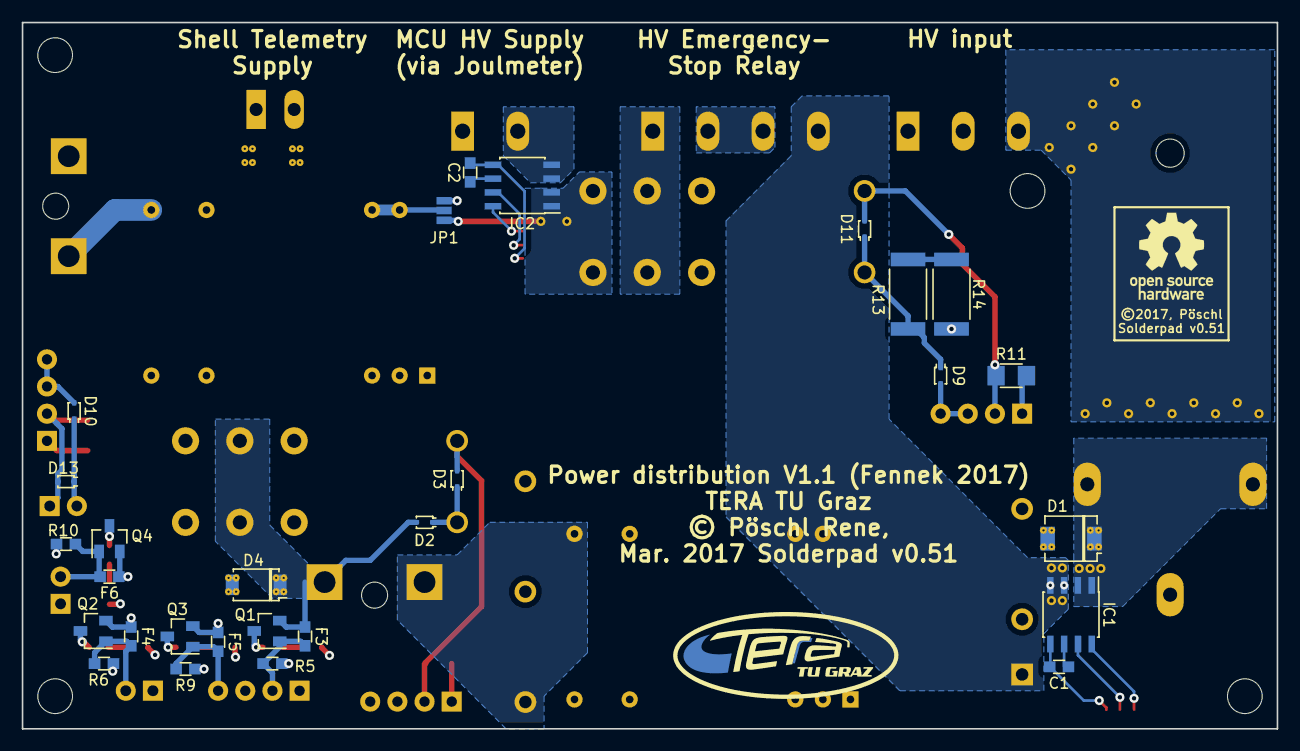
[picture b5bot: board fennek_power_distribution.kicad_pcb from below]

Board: 4 copper layers, 115.5 x 65.0 mm, 64 parts (29 on the bottom side), 48 nets.

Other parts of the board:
svg2mod: G***; TERA_Logo_SilkS_5x12.5mm
svg2mod#2: G***; TERA_Logo_SilkS_and_Cu_7.5x19mm

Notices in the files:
HW/projects/fennek_2017_18/BMS/Current_Sense/current_sense_v1_lem/current_sense.kicad_pcb:
©2017, Pöschl
HW/projects/fennek_2017_18/BMS/master_fennek18/BMS_Master_V7 -- fennek18/BMS_Master_V7_kicad.kicad_pcb:
©Pöschl, 2018
©Pöschl, Apr. 2018
HW/projects/fennek_2017_18/BMS/measurement_and_balancing/bms_board_V6-1__12s_fennek2017/bms_board.kicad_pcb:
© Pöschl Rene, Mar. 2018 Solderpad v0.51
HW/projects/fennek_2017_18/BMS/power_distribution/fennek_power_distribution_v1.1/fennek_power_distribution.kicad_pcb:
© Pöschl Rene,
Mar. 2017 Solderpad v0.51
